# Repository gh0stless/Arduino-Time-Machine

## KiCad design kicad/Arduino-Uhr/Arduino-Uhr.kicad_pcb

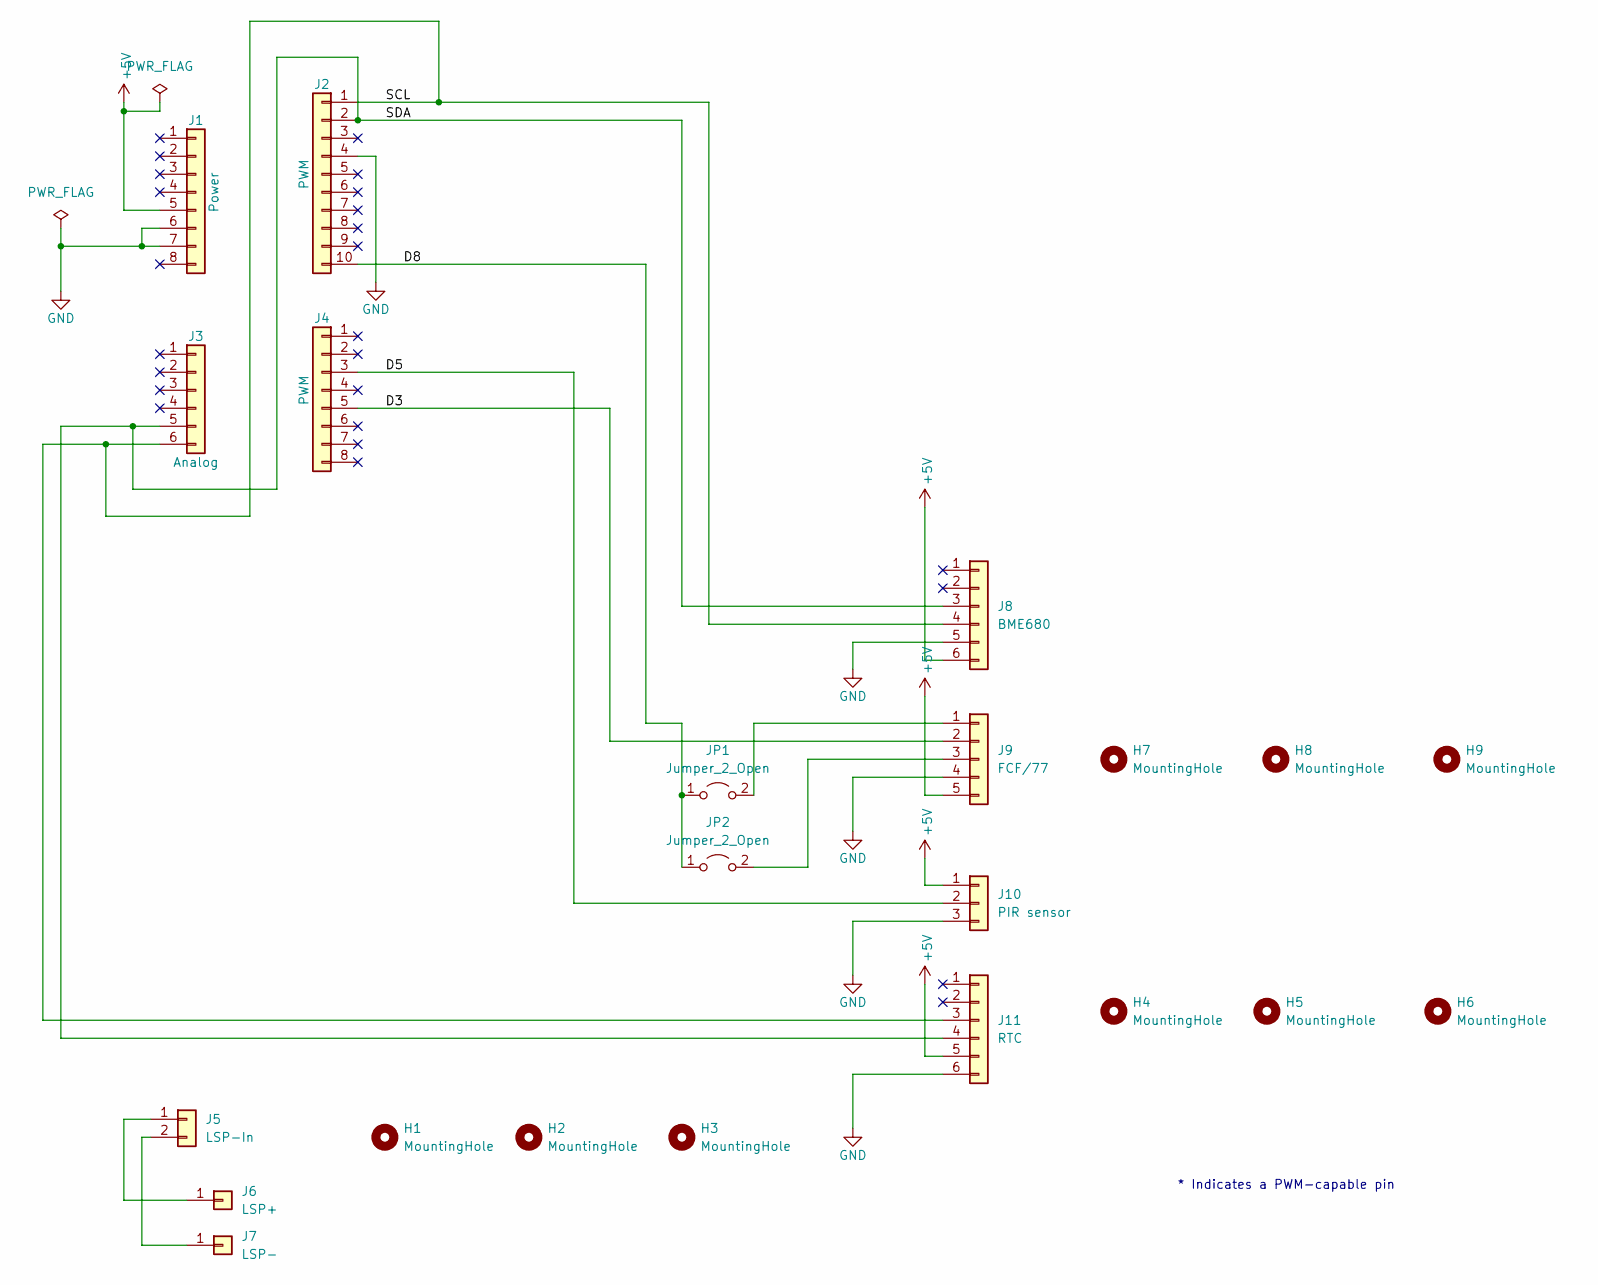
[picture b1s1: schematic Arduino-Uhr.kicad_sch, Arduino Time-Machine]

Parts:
H1, H2, H3, H4, H5, H6: MountingHole; MountingHole_3.2mm_M3_DIN965
H7, H8, H9: MountingHole; MountingHole_4.3mm_M4
J1: Power; PinSocket_1x08_P2.54mm_Vertical
J2: PWM; PinSocket_1x10_P2.54mm_Vertical
J3: Analog; PinSocket_1x06_P2.54mm_Vertical
J4: PWM; PinSocket_1x08_P2.54mm_Vertical
J5: LSP-In; PinHeader_1x02_P2.54mm_Horizontal
J6: LSP+; Pin_D1.0mm_L10.0mm_LooseFit
J7: LSP-; Pin_D1.0mm_L10.0mm_LooseFit
J8: BME680; PinSocket_1x06_P2.54mm_Horizontal
J9: FCF/77; PinSocket_1x05_P2.54mm_Horizontal
J10: PIR sensor; PinSocket_1x03_P2.54mm_Horizontal
J11: RTC; PinSocket_1x06_P2.54mm_Horizontal
JP1, JP2: Jumper_2_Open; SolderJumper-2_P1.3mm_Open_Pad1.0x1.5mm

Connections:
+5V: J1.5, J8.6, J9.5, J10.1, J11.5
/D3: J4.5, J9.2
/D5: J4.3, J10.2
/D8: J2.10, JP1.1 (A), JP2.1 (A)
/SCL: J2.1, J3.6, J8.4, J11.3
/SDA: J2.2, J3.5, J8.3, J11.4
GND: J1.6, J1.7, J2.4, J8.5, J9.4, J10.3, J11.6
unnamed: J5.1, J6.1
unnamed: J5.2, J7.1
unnamed: J9.1, JP1.2 (B)
unnamed: J9.3, JP2.2 (B)

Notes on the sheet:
* Indicates a PWM-capable pin

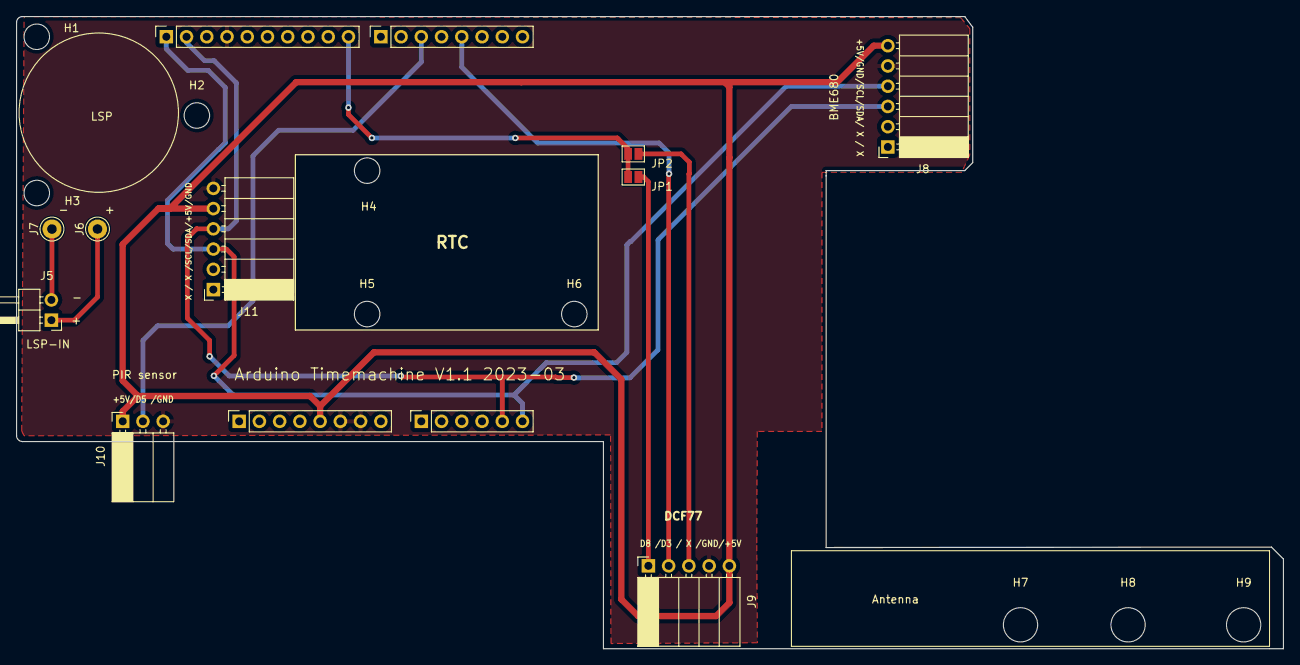
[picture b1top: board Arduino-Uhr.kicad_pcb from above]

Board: 2 copper layers, 159.0 x 79.3 mm, 22 parts (0 on the bottom side), 11 nets.

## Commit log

2021-07-15 1st commit
2021-07-15 Farben geändert von Luftgüte
2023-03-07 here we go
2023-03-10 so long
2023-03-10 mile stone
